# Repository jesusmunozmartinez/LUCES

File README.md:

# LUCES
## TFM LUCES Master SEEI
#### TITULACIÓN: Máster en Sistemas Electrónicos para Entornos Inteligentes
#### TÍTULO: "LUCES: Sistema inalámbrico de control de luminarias"
##### PALABRAS CLAVE: LUCES, ILUMINACIÓN, MESH, PCB, RED, SENSORES.
#### RESUMEN:
Este proyecto consiste en el desarrollo hardware, software y documentación de un sistema de control de iluminación inalámbrico. Este sistema permite integrar una luminaria convencional dentro de un sistema de control inteligente conectado a Internet. Su uso está orientado a la iluminación de espacios públicos como calles y parques. El control de encendido y de los niveles lumínicos de las luminarias integradas en el sistema, está basado en temporizaciones horarias, luminosidad ambiente o solar y presencia de usuarios en la vía iluminada. El sistema avisa por correo electrónico en caso de fallo de luminaria y proporciona información del consumo eléctrico, luminosidad ambiente, uso de la vía, etc. La arquitectura está basada en una red WiFi mallada con motas que controlan las luminarias y un nodo central que hace de puente con internet y proporciona el acceso a la gestión del sistema. La verificación de los requisitos se ha realizado sobre los prototipos funcionales desarrollados. Concluir que este sistema destaca por proporcionar la reducción del consumo eléctrico e inicia la posibilidad de integración de sistemas de iluminación en las “Ciudades inteligentes”. 

#### TITLE: “LIGHTS: Wireless luminaire control system”
##### KEYWORDS: LIGHTS, LIGHTING, MESH, PCB, NETWORK, SENSORS.
#### ABSTRACT:
This project consists of the development of hardware, software, and documentation of a wireless lighting control system. This system allows the integration of a conventional luminaire into an intelligent control system connected to the Internet. Its use is oriented to the lighting of public spaces such as streets and parks. The control of switching on and lighting levels of the luminaires integrated in the system is based on hourly timings, ambient or solar luminosity and the presence of users on the illuminated road. The system alerts by e-mail in case of luminaire failure and provides information on power consumption, ambient brightness, road use, etc. The architecture is based on a meshed WiFi network with motes that control the luminaires and a central node that bridges the Internet and provides access to system management. The verification of the requirements has been performed on the developed functional prototypes. To conclude that this system stands out for providing the reduction of electricity consumption and initiates the possibility of integration of lighting systems in "Smart Cities".

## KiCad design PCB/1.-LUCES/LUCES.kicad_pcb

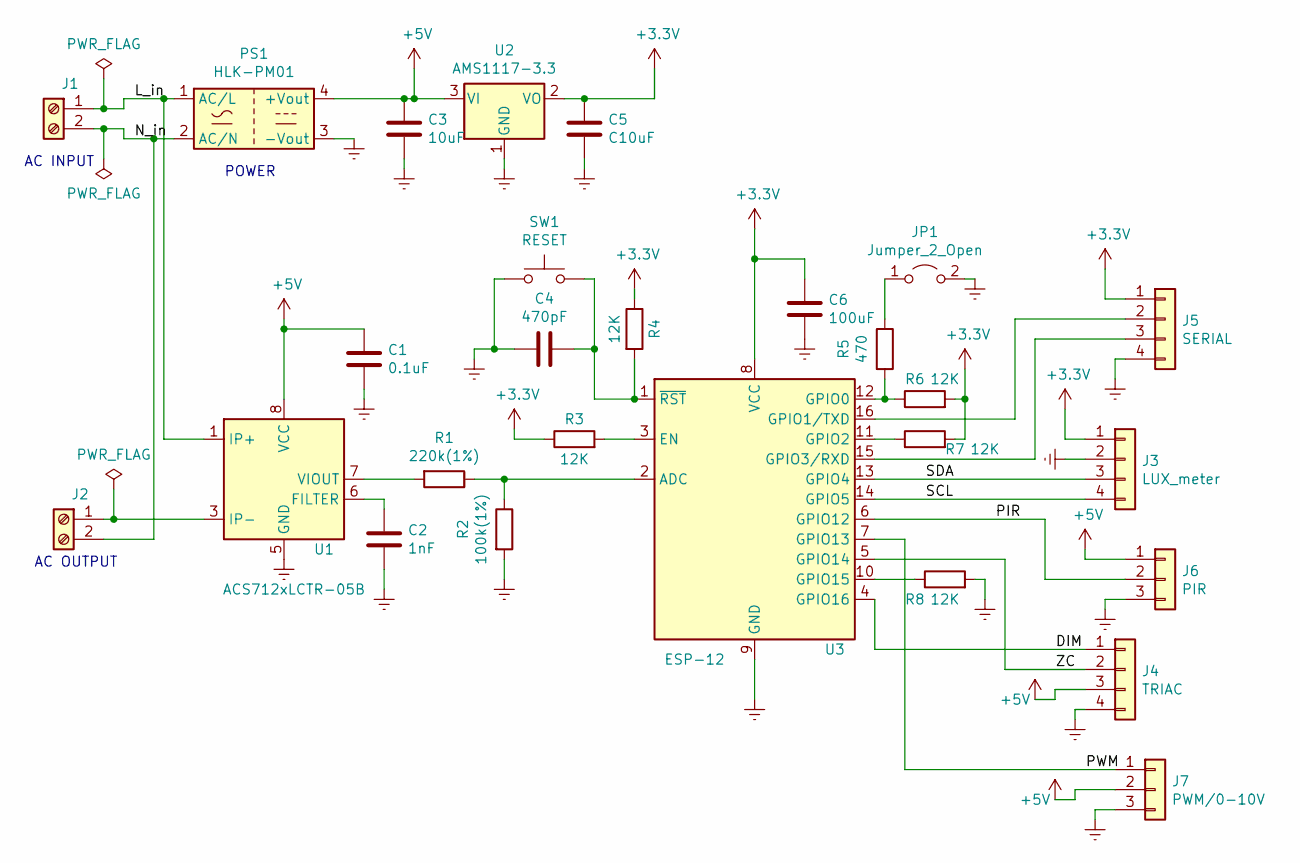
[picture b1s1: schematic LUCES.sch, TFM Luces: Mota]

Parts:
C1: 0.1uF; C_0805_2012Metric
C2: 1nF; C_0805_2012Metric
C3: 10uF; C_1206_3216Metric
C4: 470pF; C_0805_2012Metric
C5: C10uF; C_1206_3216Metric
C6: 100uF; C_0805_2012Metric
J1, J2: Screw_Terminal_01x02; TerminalBlock_Phoenix_MKDS-1,5-2_1x02_P5.00mm_Horizontal
J3: LUX_meter; JST_XH_S4B-XH-A-1_1x04_P2.50mm_Horizontal
J4: TRIAC; PinHeader_1x04_P2.54mm_Vertical
J5: SERIAL; PinHeader_1x04_P2.54mm_Vertical
J6: PIR; JST_XH_S3B-XH-A-1_1x03_P2.50mm_Horizontal
J7: PWM/0-10V; PinHeader_1x03_P2.54mm_Vertical
JP1: Jumper_2_Open; PinHeader_1x02_P2.54mm_Vertical
PS1: HLK-PM01; Converter_ACDC_HiLink_HLK-PMxx
R1: 220k(1%); R_0805_2012Metric_Pad1.20x1.40mm_HandSolder
R2: 100k(1%); R_0805_2012Metric_Pad1.20x1.40mm_HandSolder
R3, R4, R6, R7, R8: 12K; R_0805_2012Metric_Pad1.20x1.40mm_HandSolder
R5: 470; R_0805_2012Metric_Pad1.20x1.40mm_HandSolder
SW1: RESET; SW_SPST_PTS645
U1: ACS712xLCTR-05B; SOIC-8_3.9x4.9mm_P1.27mm
U2: AMS1117-3.3; SOT-223-3_TabPin2
U3: ESP-12

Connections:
+3V3: C5.1, C6.1, J3.1, J5.1, R3.1, R4.1, R6.2, R7.2, U2.2 (VO), U3.8 (VCC)
+5V: C1.1, C3.1, J4.3, J6.1, J7.2, PS1.4 (+Vout), U1.8 (VCC), U2.3 (VI)
/DIM: J4.1, U3.4 (GPIO16)
/L_in: J1.1, PS1.1 (AC/L), U1.1 (IP+), U1.2 (IP+)
/N_in: J1.2, J2.2, PS1.2 (AC/N)
/PIR: J6.2, U3.6 (GPIO12)
/PWM: J7.1, U3.7 (GPIO13)
/SCL: J3.4, U3.14 (GPIO5)
/SDA: J3.3, U3.13 (GPIO4)
/ZC: J4.2, U3.5 (GPIO14)
Earth: C1.2, C2.2, C3.2, C4.2, C5.2, C6.2, J3.2, J4.4, J5.4, J6.3, J7.3, JP1.2 (B), PS1.3 (-Vout), R2.2, R8.2, SW1.1, U1.5 (GND), U2.1 (GND), U3.9 (GND)
unnamed: C2.1, U1.6 (FILTER)
unnamed: C4.1, R4.2, SW1.2, U3.1 (~RST)
unnamed: J2.1, U1.3 (IP-), U1.4 (IP-)
unnamed: J5.2, U3.16 (GPIO1/TXD)
unnamed: J5.3, U3.15 (GPIO3/RXD)
unnamed: JP1.1 (A), R5.1
unnamed: R1.1, R2.1, U3.2 (ADC)
unnamed: R1.2, U1.7 (VIOUT)
unnamed: R3.2, U3.3 (EN)
unnamed: R5.2, R6.1, U3.12 (GPIO0)
unnamed: R7.1, U3.11 (GPIO2)
unnamed: R8.1, U3.10 (GPIO15)

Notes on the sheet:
POWER
AC INPUT
AC OUTPUT

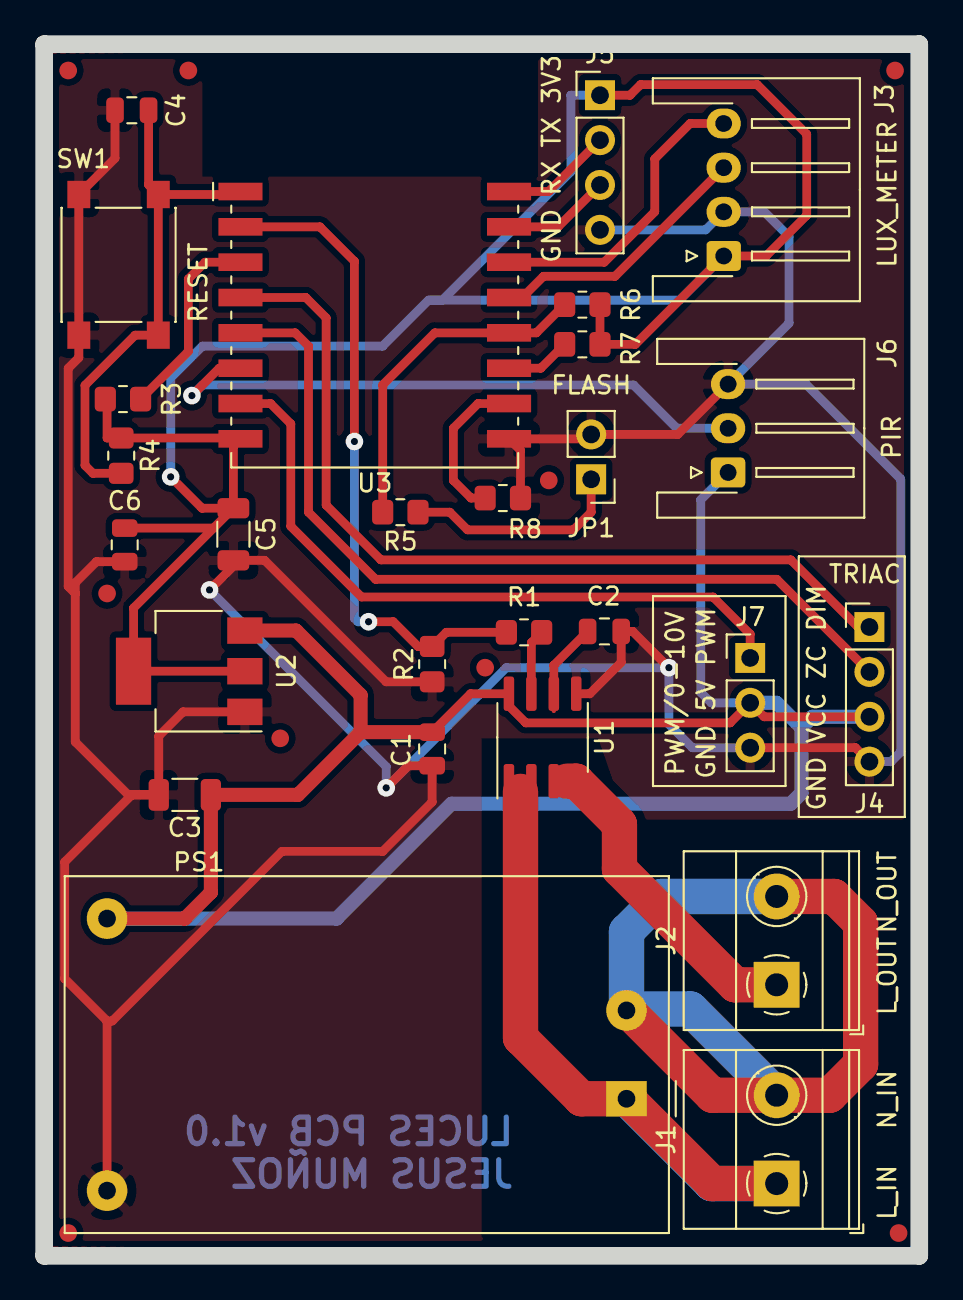
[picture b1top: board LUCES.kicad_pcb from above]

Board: 2 copper layers, 49.5 x 68.6 mm, 27 parts (0 on the bottom side), 23 nets.

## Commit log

2022-06-18 Update platformio.ini
    add board_build.filesystem = littlefs
